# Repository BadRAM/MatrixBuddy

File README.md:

A friend shaped device, using a MAX7219 driven LED matrix.

[Video Demonstration](https://www.youtube.com/watch?v=6w6y-6xS34Q)

Features:
 - Matrix Buddy posesses the GREAT EMOTIONAL STRENGTH to grin through any mood, should you need TOTAL AFFIRMATION. Press the bell to toggle, Buddy will wink to acknowledge, or blink when it is released.
 - Worried about light pollution? Matrix Buddy can read the room! Sleep mode activates in near darkness. Press the left paw to configure it's light threshold. The light sensor is on the back, make sure it's not covered.
 - Not light polluted enough? Press the right paw to configure brightness. Unleash the power of the sun!
 - Connect to a computer using the bridge program and matrix buddy can mouth along to your apps. Give a face to that cameras-off zoom call!

 To set up the Matrix Buddy Bridge app, you will first need to install the included serial drivers (CM212364_Setup.exe) and restart your computer. Run MatrixBuddyBridge.exe and press "Scan", if a device is found, you're ready, just uncheck "Mute" when you're ready for the buddy to start.

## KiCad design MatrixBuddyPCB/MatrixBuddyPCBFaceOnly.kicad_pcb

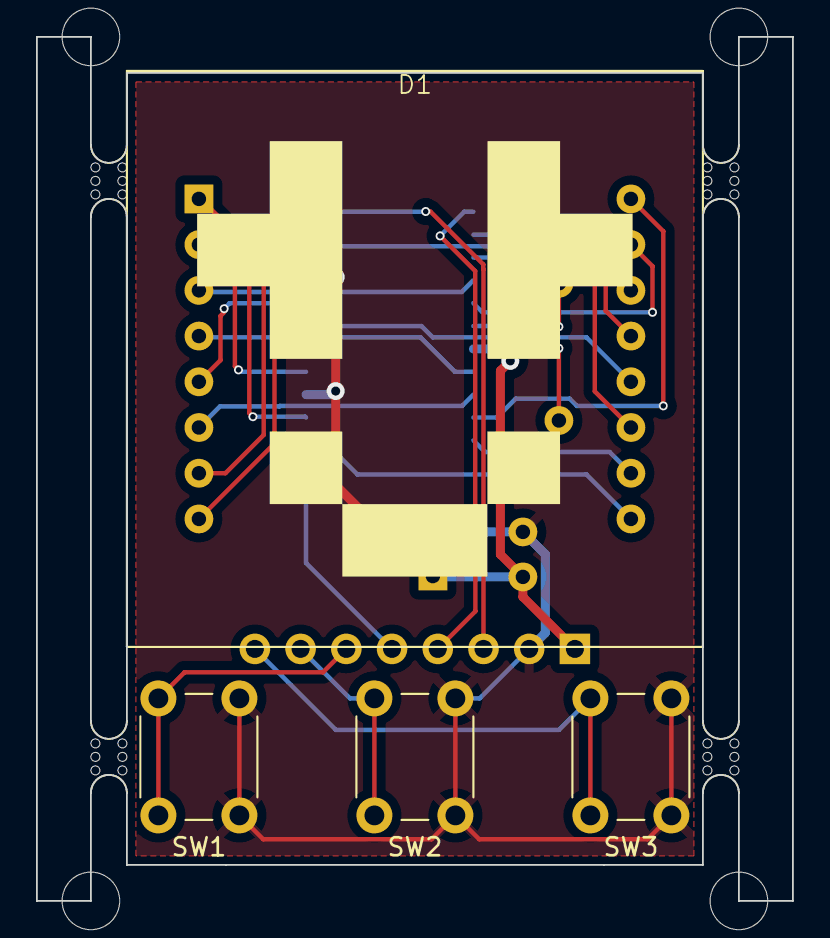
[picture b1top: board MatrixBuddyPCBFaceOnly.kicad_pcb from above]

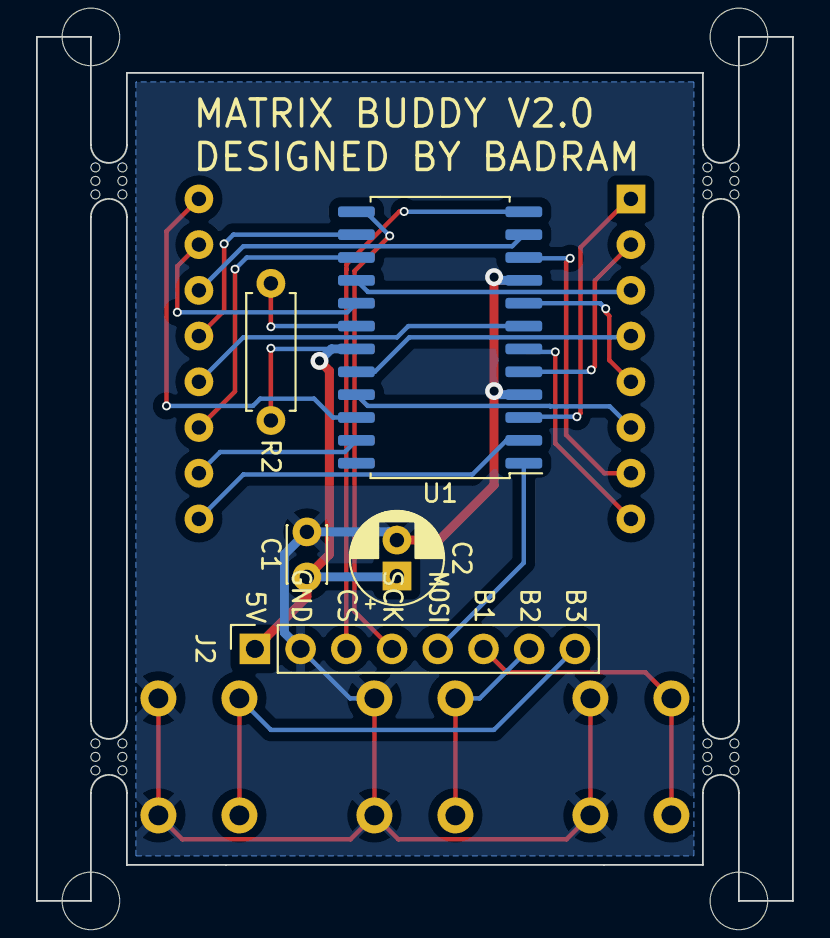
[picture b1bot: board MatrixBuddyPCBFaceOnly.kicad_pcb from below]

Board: 2 copper layers, 42.0 x 48.0 mm, 13 parts (5 on the bottom side), 25 nets.

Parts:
C1: 0.1uF; C_Disc_D3.0mm_W2.0mm_P2.50mm
C2: 10uF; CP_Radial_D5.0mm_P2.00mm
D1: 8x8 LED Matrix
J2: Conn_01x08_Socket; PinSocket_1x08_P2.54mm_Vertical
R2: 47K; R_Axial_DIN0207_L6.3mm_D2.5mm_P7.62mm_Horizontal
SW1, SW2, SW3: SW_Push; SW_PUSH_6mm
U1: MAX7221xWG; SOIC-24W_7.5x15.4mm_P1.27mm
mouse-bite-2mm-slot, mouse-bite-2mm-slot#2, mouse-bite-2mm-slot#3, mouse-bite-2mm-slot#4: VAL**; mouse-bite-2mm-slot

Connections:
+5V: C1.1, C2.1, J2.1, R2.1, U1.19 (V+)
COL1: D1.13 (Col1), U1.14 (SEG_A)
COL2: D1.3 (Col2), U1.16 (SEG_B)
COL3: D1.4 (Col3), U1.20 (SEG_C)
COL4: D1.10 (Col4), U1.23 (SEG_D)
COL5: D1.6 (Col5), U1.21 (SEG_E)
COL6: D1.11 (Row6), U1.15 (SEG_F)
COL7: D1.15 (Col7), U1.17 (SEG_G)
COL8: D1.16 (Col8), U1.22 (SEG_DP)
Earth: C1.2, C2.2, J2.2, SW1.2, SW2.2, SW3.2, U1.4 (GND), U1.9 (GND)
unnamed: J2.3, U1.12 (~CS)
unnamed: J2.4, U1.13 (CLK)
unnamed: J2.5, U1.1 (DIN)
unnamed: J2.6, SW1.1
unnamed: J2.7, SW2.1
unnamed: J2.8, SW3.1
unnamed: R2.2, U1.18 (ISET)
ROW1: D1.9 (Row1), U1.2 (DIG_0)
ROW2: D1.14 (Row2), U1.11 (DIG_1)
ROW3: D1.8 (Row3), U1.6 (DIG_2)
ROW4: D1.12 (Row4), U1.7 (DIG_3)
ROW5: D1.1 (Row5), U1.3 (DIG_4)
ROW6: D1.7 (Col6), U1.10 (DIG_5)
ROW7: D1.2 (Row7), U1.5 (DIG_6)
ROW8: D1.5 (Row8), U1.8 (DIG_7)

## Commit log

2023-11-30 CAD for shell and stls for printing
2023-12-02 multi material printing overhaul!
2023-12-02 ears rework
2023-12-10 Refactored firmware to use non blocking animations via event queue system, added brightness setting GUI
2023-12-10 added sleep threshold config screen and emotional strength mode
2023-12-10 added timeout to wakeup
2023-12-11 implemented emotional strength mode
2023-12-14 reorganized files and added Bridge app
2023-12-14 expanded readme.md
2023-12-15 matrix buddy link to bridge app implemented.
2023-12-16 fixed ear sneeze in MatrixBuddyShell print settings
2023-12-16 Fixed bug where MatrixBuddyBridge would fail to detect connected buddy because of arduino's serial auto-reset feature.
2023-12-23 created box stencil, started on instruction manual.
2023-12-31 finished instruction booklet
2023-12-31 Buddy bridge update, with documentation on README
2024-02-08 updated gitignore
2024-02-08 Designed PCB for production
2024-02-10 pcb v2.0 final
2024-03-10 Bugfixing ahead of first production batch.
2024-04-19 fixed bug that prevented brightness and other settings from being saved between power cycles.
